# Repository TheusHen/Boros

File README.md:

# Boros Rocket

*Amateur rocket created by an 15 year old teenager.*

This repository contains the current **Beta** state of the Boros rocket avionics stack.  
The project has already passed **Pre-Alpha** and **Alpha** stages and is now focused on stabilizing hardware-software integration with the **Plate PCB version**.

## Current Focus

- Firmware flight logging and fault handling (`firmware/`)
- Physics-based flight simulation and Monte Carlo (`sim/flight/`)
- PCB design and manufacturing outputs (`PCB/plate_version/`)
- CI pipeline with firmware build, simulation, and reporting (`.github/workflows/ci.yml`)

## Hardware Direction (Plate Version)

We are using the **Plate PCB** approach (not the Coin version), currently at **V4 (2 layers)**.

### PCB and 3D previews

### PCB iteration history (Plate)

## Mass Budget Baseline (Plate)

The mass budget tool is used to estimate liftoff mass from:

- Rocket 3D model volume
- Motor mass: **24.1 g**
- PCB plate geometry: **25 mm x 62 mm**, **2 copper layers**
- Motor limit check: **113 g max liftoff mass**

Run:

```bash
make python-mass-budget
```

Outputs:

- `sim/flight/out/mass_budget.json`
- `sim/flight/out/mass_budget.md`

## Simulation Workflow

The Python simulation now consumes the mass budget output and uses the suggested total mass automatically.

Run:

```bash
make python-sim
```

This generates:

- Flight timeseries and summary
- Monte Carlo summary
- Firmware-like sensor log for playback/testing

## Quick Commands

```bash
make firmware
make python-check
make python-sim
make python-firmware-playback
make python-mass-budget
```

## Notes

- The repository includes both firmware and simulation assets to support rapid iteration.
- CI publishes simulation and firmware validation artifacts for each run.

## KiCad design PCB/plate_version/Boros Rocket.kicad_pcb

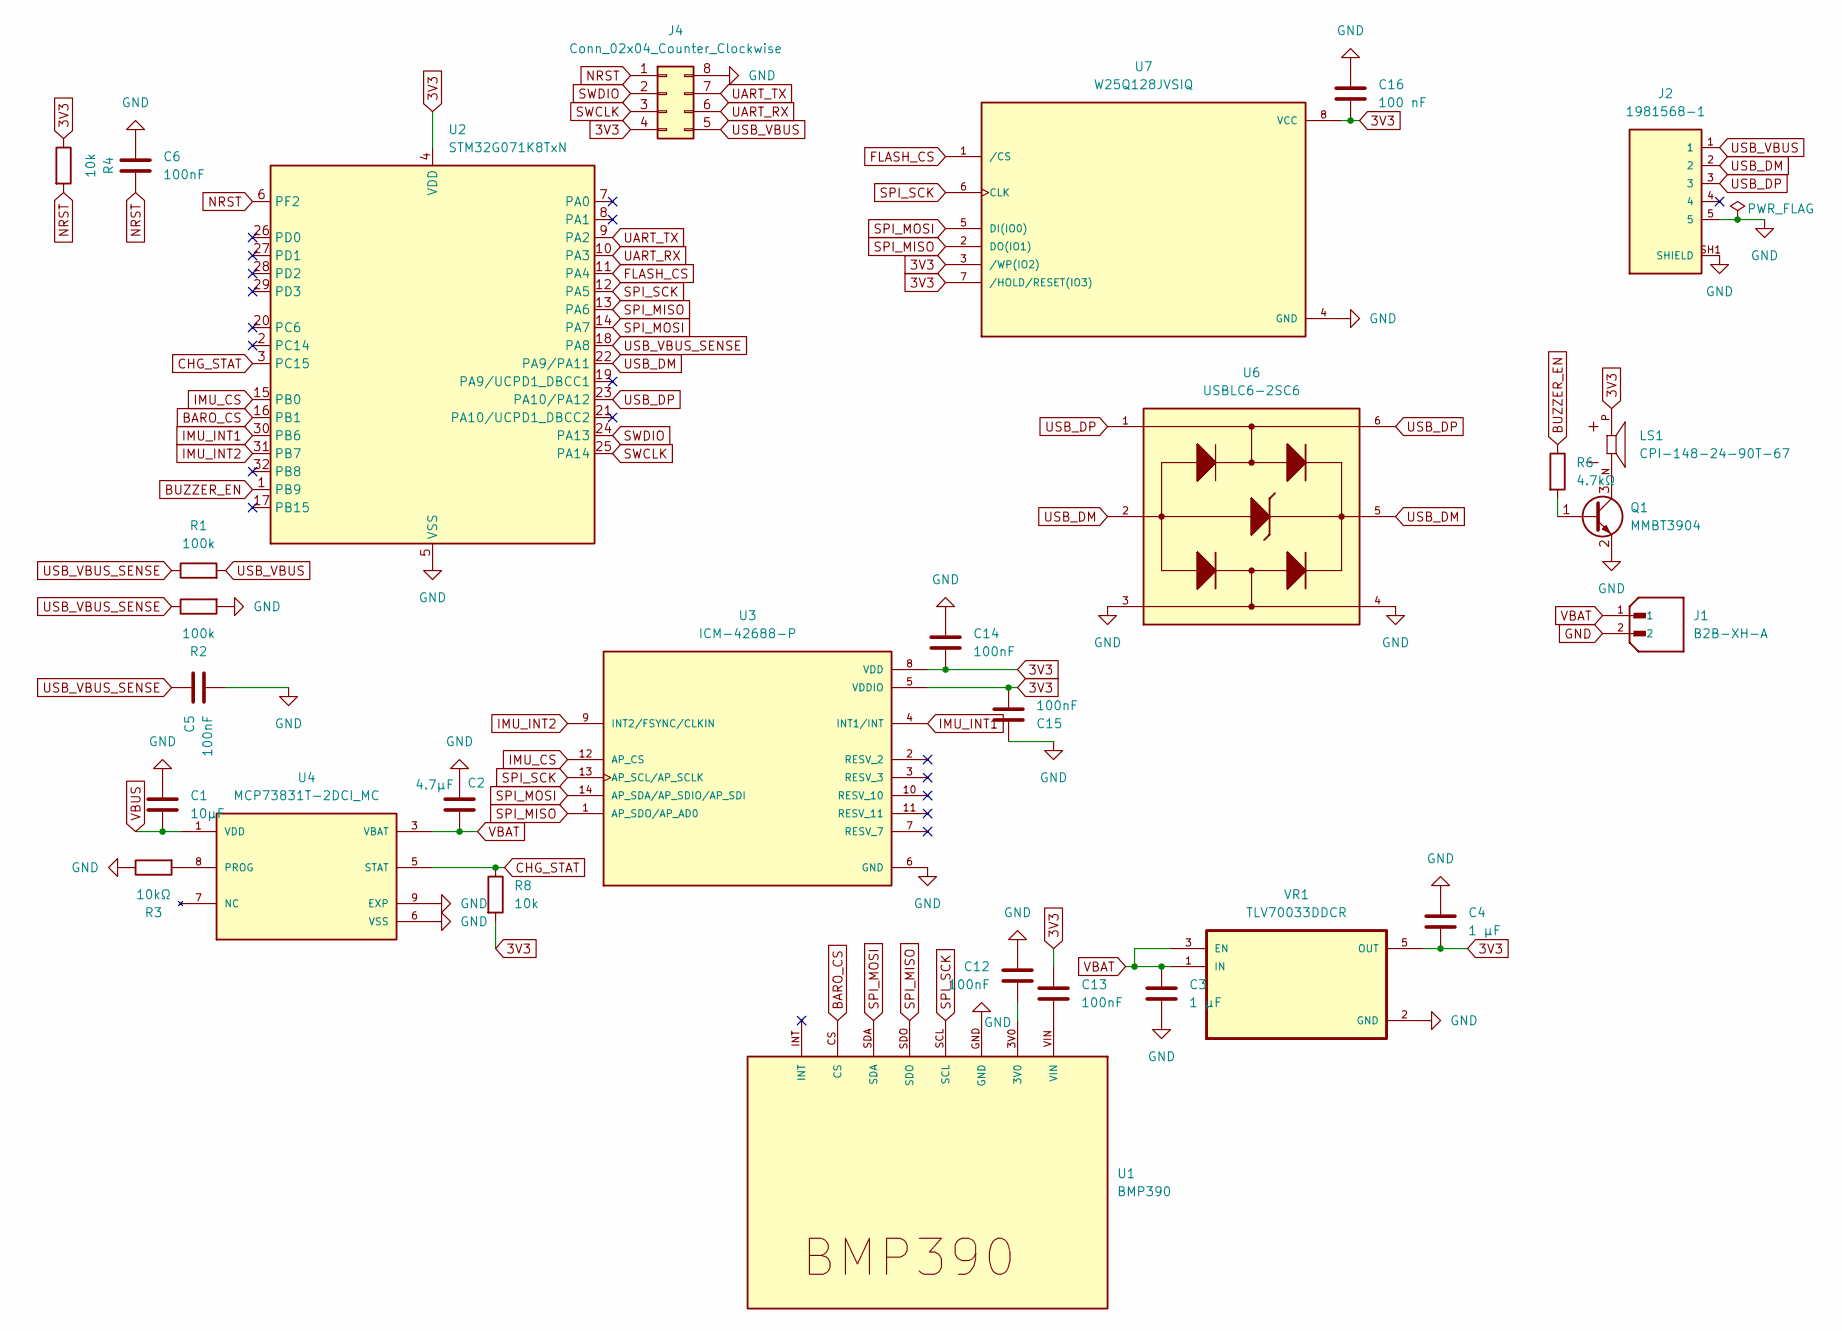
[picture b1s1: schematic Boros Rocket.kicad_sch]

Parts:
C1: 10µF; C_0805_2012Metric
C2: 4.7µF; C_0805_2012Metric
C3, C4: 1 µF; C_0603_1608Metric
C5, C6, C12, C13, C14, C15: 100nF; C_0603_1608Metric
C16: 100 nF; C_0603_1608Metric
J1: B2B-XH-A; JST_B2B-XH-A; PARTREV N/A
J2: 1981568-1; TE_1981568-1; PARTREV E3
J4: Conn_02x04_Counter_Clockwise; PinHeader_2x04_P2.54mm_Vertical
LS1: CPI-148-24-90T-67; XDCR_CPI-148-24-90T-67; PARTREV 1
Q1: MMBT3904; SOT-23
R1, R2: 100k; R_0603_1608Metric
R3: 10kΩ; R_0603_1608Metric
R4, R8: 10k; R_0603_1608Metric
R6: 4.7kΩ; R_0603_1608Metric
U1: BMP390
U2: STM32G071K8TxN; LQFP-32_7x7mm_P0.8mm
U3: ICM-42688-P; PQFN50P300X250X97-14N; PARTREV 1.2
U4: MCP73831T-2DCI_MC; SON50P200X300X100-9N; PARTREV H
U6: USBLC6-2SC6; SOT95P280X145-6N
U7: W25Q128JVSIQ; SOIC127P790X216-8N; PARTREV I
VR1: TLV70033DDCR; SOT95P280X110-5N

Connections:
3V3: C4.2, C13.1, C14.2, C15.2, C16.2, J4.4, LS1.P, R4.1, R8.2, U2.4 (VDD), U3.5 (VDDIO), U3.8 (VDD), U7.3 (/WP(IO2)), U7.7 (/HOLD/RESET(IO3)), U7.8 (VCC), VR1.5 (OUT)
BARO_CS: U1.CS, U2.16 (PB1)
BUZZER_EN: R6.1, U2.1 (PB9)
CHG_STAT: R8.1, U2.3 (PC15), U4.5 (STAT)
FLASH_CS: U2.11 (PA4), U7.1 (/CS)
GND: C1.1, C2.1, C3.1, C4.1, C5.1, C6.2, C12.1, C14.1, C15.1, C16.1, J1.2, J2.5, J2.SH1 (SHIELD), J2.SH2 (SHIELD), J2.SH3 (SHIELD), J2.SH4 (SHIELD), J2.SH5 (SHIELD), J2.SH6 (SHIELD), J4.8, Q1.2 (E), R2.2, R3.1, U1.GND, U2.5 (VSS), U3.6 (GND), U4.6 (VSS), U4.9 (EXP), U6.3, U6.4, U7.4 (GND), VR1.2 (GND)
IMU_CS: U2.15 (PB0), U3.12 (AP_CS)
IMU_INT1: U2.30 (PB6), U3.4 (INT1/INT)
IMU_INT2: U2.31 (PB7), U3.9 (INT2/FSYNC/CLKIN)
NRST: C6.1, J4.1, R4.2, U2.6 (PF2)
unnamed: C12.2, U1.3V0
unnamed: C13.2, U1.VIN
unnamed: Q1.1 (B), R6.2
unnamed: LS1.N, Q1.3 (C)
unnamed: R3.2, U4.8 (PROG)
SPI_MISO: U1.SDO, U2.13 (PA6), U3.1 (AP_SDO/AP_AD0), U7.2 (DO(IO1))
SPI_MOSI: U1.SDA, U2.14 (PA7), U3.14 (AP_SDA/AP_SDIO/AP_SDI), U7.5 (DI(IO0))
SPI_SCK: U1.SCL, U2.12 (PA5), U3.13 (AP_SCL/AP_SCLK), U7.6 (CLK)
SWCLK: J4.3, U2.25 (PA14)
SWDIO: J4.2, U2.24 (PA13)
UART_RX: J4.6, U2.10 (PA3)
UART_TX: J4.7, U2.9 (PA2)
USB_DM: J2.2, U2.22 (PA9/PA11), U6.2, U6.5
USB_DP: J2.3, U2.23 (PA10/PA12), U6.1, U6.6
USB_VBUS: J2.1, J4.5, R1.2
USB_VBUS_SENSE: C5.2, R1.1, R2.1, U2.18 (PA8)
VBAT: C2.2, C3.2, J1.1, U4.3 (VBAT), U4.4 (VBAT), VR1.1 (IN), VR1.3 (EN)
VBUS: C1.2, U4.1 (VDD), U4.2 (VDD)

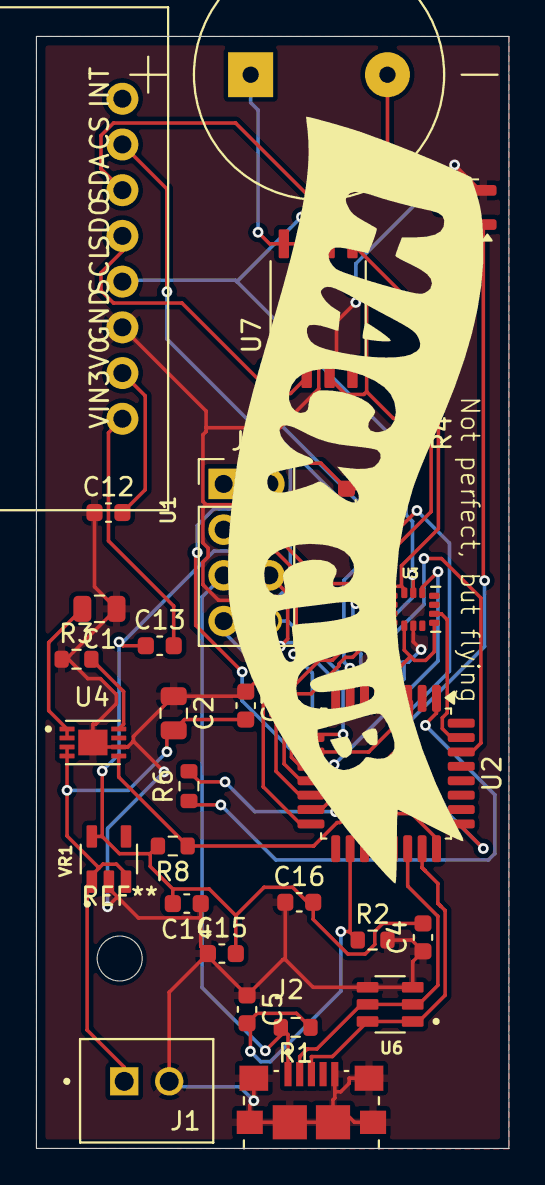
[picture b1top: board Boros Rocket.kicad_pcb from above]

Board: 2 copper layers, 26.3 x 61.8 mm, 29 parts (0 on the bottom side), 28 nets.

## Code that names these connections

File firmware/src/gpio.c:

// gpio.c
#include "stm32g071.h"
#include "gpio.h"

// SPI1: PA5 SCK, PA6 MISO, PA7 MOSI
// CS: PA4 FLASH_CS, PB0 IMU_CS, PB1 BARO_CS
// BUZZER: PB9
// UART2: PA2 TX, PA3 RX (AF1)
// USB: PA11/PA12
// Status inputs: PA8 USB_VBUS_SENSE, PC15 CHG_STAT, PB6 IMU_INT1, PB7 IMU_INT2

static inline void gpio_mode(GPIO_TypeDef* p, int pin, int mode) {
  p->MODER = (p->MODER & ~(3u << (pin*2))) | ((uint32_t)mode << (pin*2));
}
static inline void gpio_af(GPIO_TypeDef* p, int pin, int af) {
  if (pin < 8) {
    p->AFRL = (p->AFRL & ~(0xFu << (pin*4))) | ((uint32_t)af << (pin*4));
  } else {
    int p8 = pin - 8;
    p->AFRH = (p->AFRH & ~(0xFu << (p8*4))) | ((uint32_t)af << (p8*4));
  }
}

void gpio_init_all(void) {
  gpio_mode(GPIOA, 4, 1);
  gpio_mode(GPIOB, 0, 1);
  gpio_mode(GPIOB, 1, 1);
  gpio_mode(GPIOB, 9, 1);

  cs_flash(1);
  cs_imu(1);
  cs_baro(1);

  gpio_mode(GPIOA, 5, 2);
  gpio_mode(GPIOA, 6, 2);
  gpio_mode(GPIOA, 7, 2);
  gpio_af(GPIOA, 5, 0);
  gpio_af(GPIOA, 6, 0);
  gpio_af(GPIOA, 7, 0);

  gpio_mode(GPIOA, 2, 2);
  gpio_mode(GPIOA, 3, 2);
  gpio_af(GPIOA, 2, 1);
  gpio_af(GPIOA, 3, 1);

  gpio_mode(GPIOA, 8, 0);
  gpio_mode(GPIOC, 15, 0);
  gpio_mode(GPIOB, 6, 0);
  gpio_mode(GPIOB, 7, 0);
}

void cs_flash(int level) { if (level) GPIOA->BSRR = (1u<<4); else GPIOA->BSRR = (1u<<(4+16)); }
void cs_imu(int level)   { if (level) GPIOB->BSRR = (1u<<0); else GPIOB->BSRR = (1u<<(0+16)); }
void cs_baro(int level)  { if (level) GPIOB->BSRR = (1u<<1); else GPIOB->BSRR = (1u<<(1+16)); }

void buzzer_set(int on)  { if (on) GPIOB->BSRR = (1u<<9); else GPIOB->BSRR = (1u<<(9+16)); }

int usb_vbus_sense_read(void) { return (GPIOA->IDR >> 8) & 1u; }
int chg_stat_read(void)       { return (GPIOC->IDR >> 15) & 1u; }
int imu_int1_read(void)       { return (GPIOB->IDR >> 6) & 1u; }
int imu_int2_read(void)       { return (GPIOB->IDR >> 7) & 1u; }

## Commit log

2026-02-21 Add new component symbols and simulation scripts
    - Added USBLC6-2SC6 symbol to the KiCad library.
    - Added W25Q128JVSIQ symbol to the KiCad library.
    - Added W25Q32JVSSIQ symbol to the KiCad library.
    - Created new simulation scripts for 3D aerodynamics and flight dynamics, including:
    - aero_coefficients.m
    - aerodinamics.m
2026-02-21 Refactor code structure for improved readability and maintainability
2026-02-21 Add firmware support for BMP390 and ICM42688 sensors
    - Implemented BMP390 driver for pressure and temperature readings.
    - Added ICM42688 driver for accelerometer and gyroscope data acquisition.
    - Introduced SPI communication functions for sensor interaction.
    - Created GPIO management functions for chip select and buzzer control.
    - Developed logging functionality to record sensor data and system status.
    - Set up UART for communication and debugging output.
2026-02-21 feat: Implement flight simulation and logging features
    - Added sensor models for generating firmware-like logs in `sensor_models.py`.
    - Developed a simulation script in `simulate.py` to run flight simulations and output results.
    - Created tests for constant drag and no drag scenarios in `test_constant_drag.py` and `test_no_drag.py`.
    - Introduced CI workflow in `.github/workflows/ci.yml` for automated testing and firmware builds.
    - Added Makefile for build automation and simplified command execution.
    - Implemented MATLAB/Octave 3D simulation runner in `run_ci_sim.m`.
2026-02-21 chore: Remove outdated README.md for simulation directory
2026-02-21 feat: Enhance logging and flash memory management, add trapezoidal integration function
2026-02-21 Add logging functionality, SPI communication, and telemetry dump tool
    - Created log.h for logging flags and log record structure.
    - Implemented SPI communication in spi.c for SPI1 initialization and data transfer.
    - Developed a Python script (dump.py) for capturing telemetry data over UART with automatic port detection and CSV output.
    - Added requirements.txt to specify the pyserial dependency for the telemetry dump tool.
2026-02-21 fix: Update Makefile to ensure proper dependency order for ci and check targets
2026-02-21 fix: Correct ARM GCC path in CI workflow
2026-02-21 fix: Optimize data initialization in Reset_Handler for better performance
2026-02-21 fix: Update linker script to properly discard C++ exception tables and define heap start symbol
2026-02-21 feat: Enhance CI workflow with Python simulation artifact handling and firmware playback summary
2026-02-21 fix: Update RecoveryConfig parameters for optimal rocket performance and enhance JSON loading functions in CI report
2026-02-21 Add Gerber job file for Boros Rocket PCB design
    - Created a new Gerber job file 'Boros Rocket-job.gbrjob' for the Boros Rocket project.
    - Included project specifications such as size, layer number, and board thickness.
    - Defined design rules for outer and inner layers.
    - Specified file attributes for copper layers, solder masks, silkscreens, and assembly drawings.
    - Documented material stackup including thickness and type for each layer.
2026-02-21 fix: Remove obsolete NPTH drill and Gerber files from the PCB directory
2026-02-21 Refactor code structure for improved readability and maintainability
    Remaking Rocket again(3D)
2026-02-21 Add mass budget computation tool for STL, motor, and PCB plate
    - Implemented a new script `mass_budget.py` to calculate the mass budget based on STL geometry, motor specifications, and PCB plate details.
    - The script includes functionality to generate both JSON and Markdown outputs summarizing the mass budget.
    - Added command-line arguments for user input, including STL path, motor mass, airframe density, and PCB specifications.
    - Integrated functions to convert units and calculate various mass components, including airframe, PCB, and total estimated liftoff mass.
2026-02-21 Refactor code structure for improved readability and maintainability
    Implemented V4 PCB!
2026-02-21 fix: Version imagem error
2026-02-21 Add caching for Python dependencies in CI workflow
2026-03-07 Fixed 3D
2026-03-21 Add new components to bom_mouser.csv
    Added new components to the BOM from Mouser, including various capacitors, resistors, sensors, and microcontrollers.
2026-03-21 Remove duplicate line in bom_mouser.csv
2026-03-21 Revise bom_mouser.csv with headers and descriptions
    Updated the BOM file format to include headers and improved component descriptions.
2026-03-21 Create bom_total.csv with component details
    Added a bill of materials (BOM) with components, pricing, and notes.
